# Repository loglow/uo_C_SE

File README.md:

# µo_C SE (uo_C, Ornament & Crime) Eurorack [Rev B]

## 8HP Eurorack module | Polymorphic CV generator

[μo_C SE](http://uoc-se.com) is a multi-purpose module in which a generic set of inputs and outputs are remapped on-the-fly through the use of a number of different built-in apps.

This re-engineered Eurorack module updates and simplifies the classic [Ornament & Crime](http://ornament-and-cri.me/) (aka o_C) design by miniaturizing the module from 14HP to 8HP and redesigning the front panel layout without eliminating any functionality.

Fully compatible with upstream o_C firmware. Includes power cable, mounting hardware, and a one-year warranty. Designed and built with care by [Tall Dog Electronics](http://tall-dog.com) in Western Massachusetts. Licensed [CC BY-NC-SA 4.0](https://creativecommons.org/licenses/by-nc-sa/4.0/) open source hardware.

- **Height:** 3U (128.5 mm)
- **Width:** 8HP (40.3 mm)
- **Depth:** 31 mm (with power)
- **+12V:** 85 mA (average)
- **-12V:** 10 mA (average)

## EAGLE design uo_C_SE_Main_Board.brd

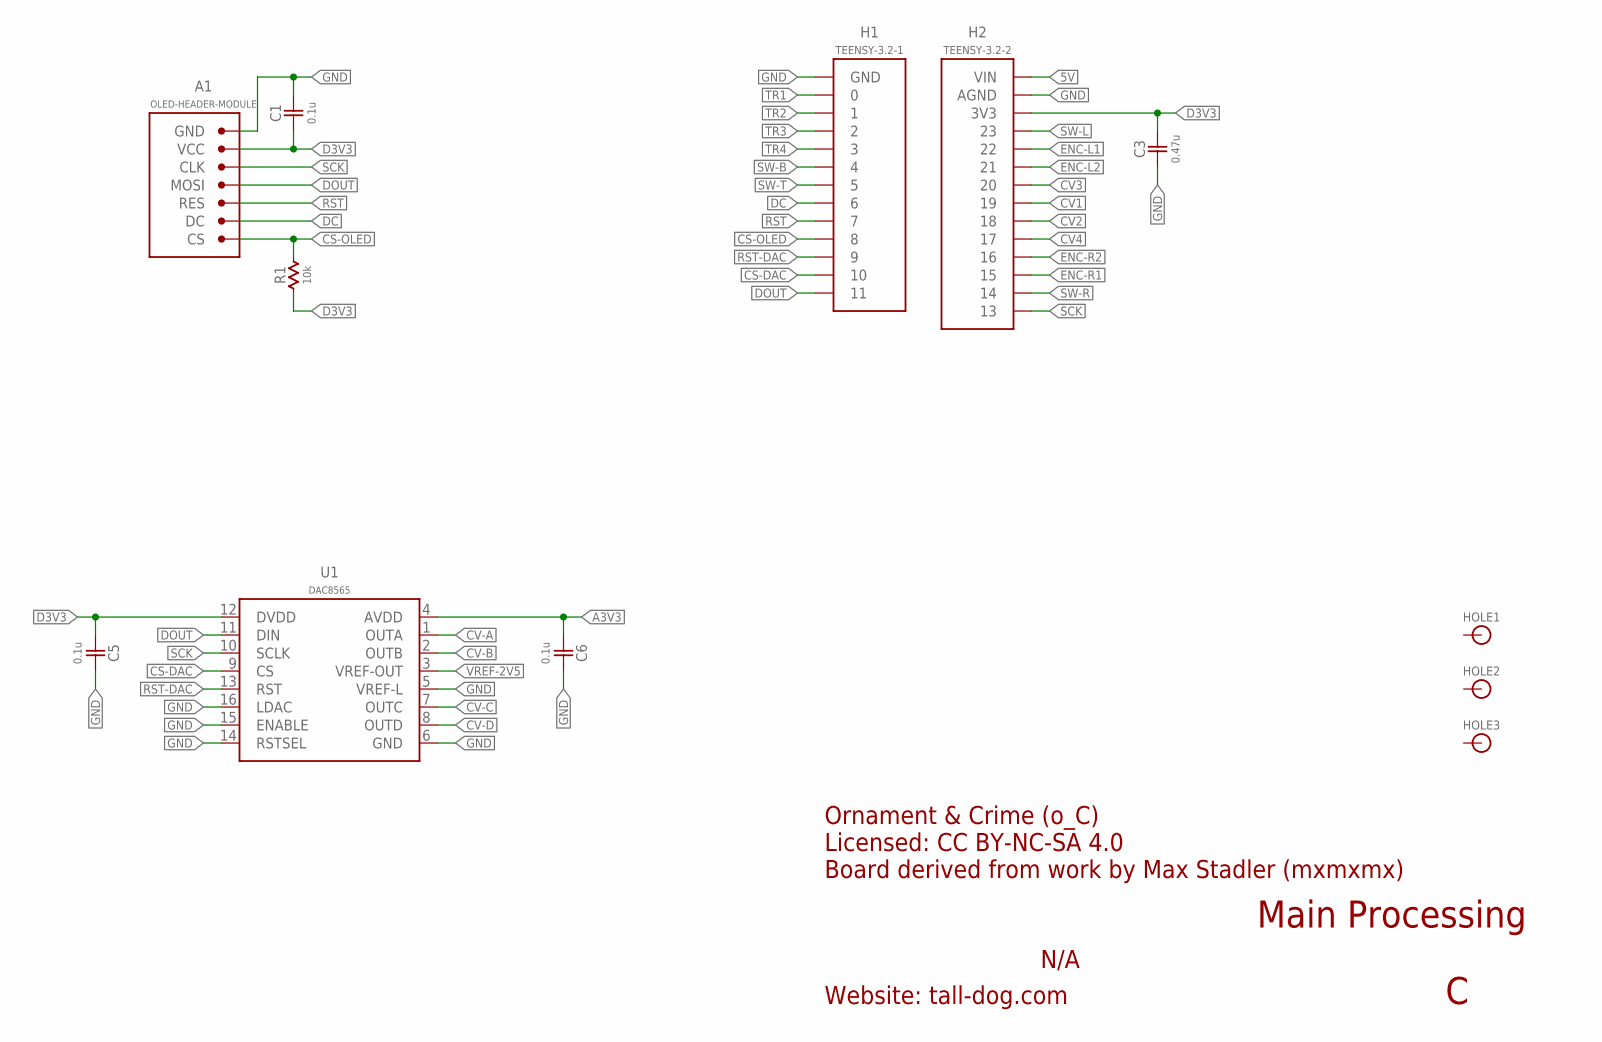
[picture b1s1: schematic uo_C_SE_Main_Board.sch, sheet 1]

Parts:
A1: OLED-HEADER-MODULE; DISPLAY-MODULE; MANUFACTURERPARTNUMBER TD-OCSE-B-DM
C1, C5, C6: 0.1u; 0603-NP; MANUFACTURERPARTNUMBER CL10B104JB8NNNC
C3: 0.47u; 0603-NP; MANUFACTURERPARTNUMBER CL10B474KA8NFNC
H1: TEENSY-3.2-1; SMD-0.1-1X13; MANUFACTURERPARTNUMBER TSM-113-04-L-SV
H2: TEENSY-3.2-2; SMD-0.1-1X14; MANUFACTURERPARTNUMBER TSM-114-04-L-SV
HOLE1, HOLE2, HOLE3: HOLE; M2.5-HOLE
R1: 10k; 0603-NP; MANUFACTURERPARTNUMBER ERJ-3EKF1002V
U1: DAC8565; TSSOP-16; MANUFACTURERPARTNUMBER DAC8565IAPW

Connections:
5V: H2.1 (VIN); also elsewhere on the board
A3V3: C6.1, U1.4 (AVDD); also elsewhere on the board
CS-DAC: H1.12 (10), U1.9 (CS)
CS-OLED: A1.7 (CS), H1.10 (8), R1.2
CV1: H2.8 (19); also elsewhere on the board
CV2: H2.9 (18); also elsewhere on the board
CV3: H2.7 (20); also elsewhere on the board
CV4: H2.10 (17); also elsewhere on the board
CV-A: U1.1 (OUTA); also elsewhere on the board
CV-B: U1.2 (OUTB); also elsewhere on the board
CV-C: U1.7 (OUTC); also elsewhere on the board
CV-D: U1.8 (OUTD); also elsewhere on the board
D3V3: A1.2 (VCC), C1.1, C3.2, C5.1, H2.3 (3V3), R1.1, U1.12 (DVDD)
DC: A1.6 (DC), H1.8 (6)
DOUT: A1.4 (MOSI), H1.13 (11), U1.11 (DIN)
ENC-L1: H2.5 (22); also elsewhere on the board
ENC-L2: H2.6 (21); also elsewhere on the board
ENC-R1: H2.12 (15); also elsewhere on the board
ENC-R2: H2.11 (16); also elsewhere on the board
GND: A1.1 (GND), A1.G1 (GND), A1.G2 (GND), A1.G3 (GND), A1.G4 (GND), A1.G5 (GND), A1.G6 (GND), C1.2, C3.1, C5.2, C6.2, H1.1 (GND), H2.2 (AGND), U1.5 (VREF-L), U1.6 (GND), U1.14 (RSTSEL), U1.15 (ENABLE), U1.16 (LDAC); also elsewhere on the board
RST: A1.5 (RES), H1.9 (7)
RST-DAC: H1.11 (9), U1.13 (RST)
SCK: A1.3 (CLK), H2.14 (13), U1.10 (SCLK)
SW-B: H1.6 (4); also elsewhere on the board
SW-L: H2.4 (23); also elsewhere on the board
SW-R: H2.13 (14); also elsewhere on the board
SW-T: H1.7 (5); also elsewhere on the board
TR1: H1.2 (0); also elsewhere on the board
TR2: H1.3 (1); also elsewhere on the board
TR3: H1.4 (2); also elsewhere on the board
TR4: H1.5 (3); also elsewhere on the board
VREF-2V5: U1.3 (VREF-OUT); also elsewhere on the board

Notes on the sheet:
Ornament & Crime (o_C) Licensed: CC BY-NC-SA 4.0 Board derived from work by Max Stadler (mxmxmx)
Website: tall-dog.com
N/A
Main Processing

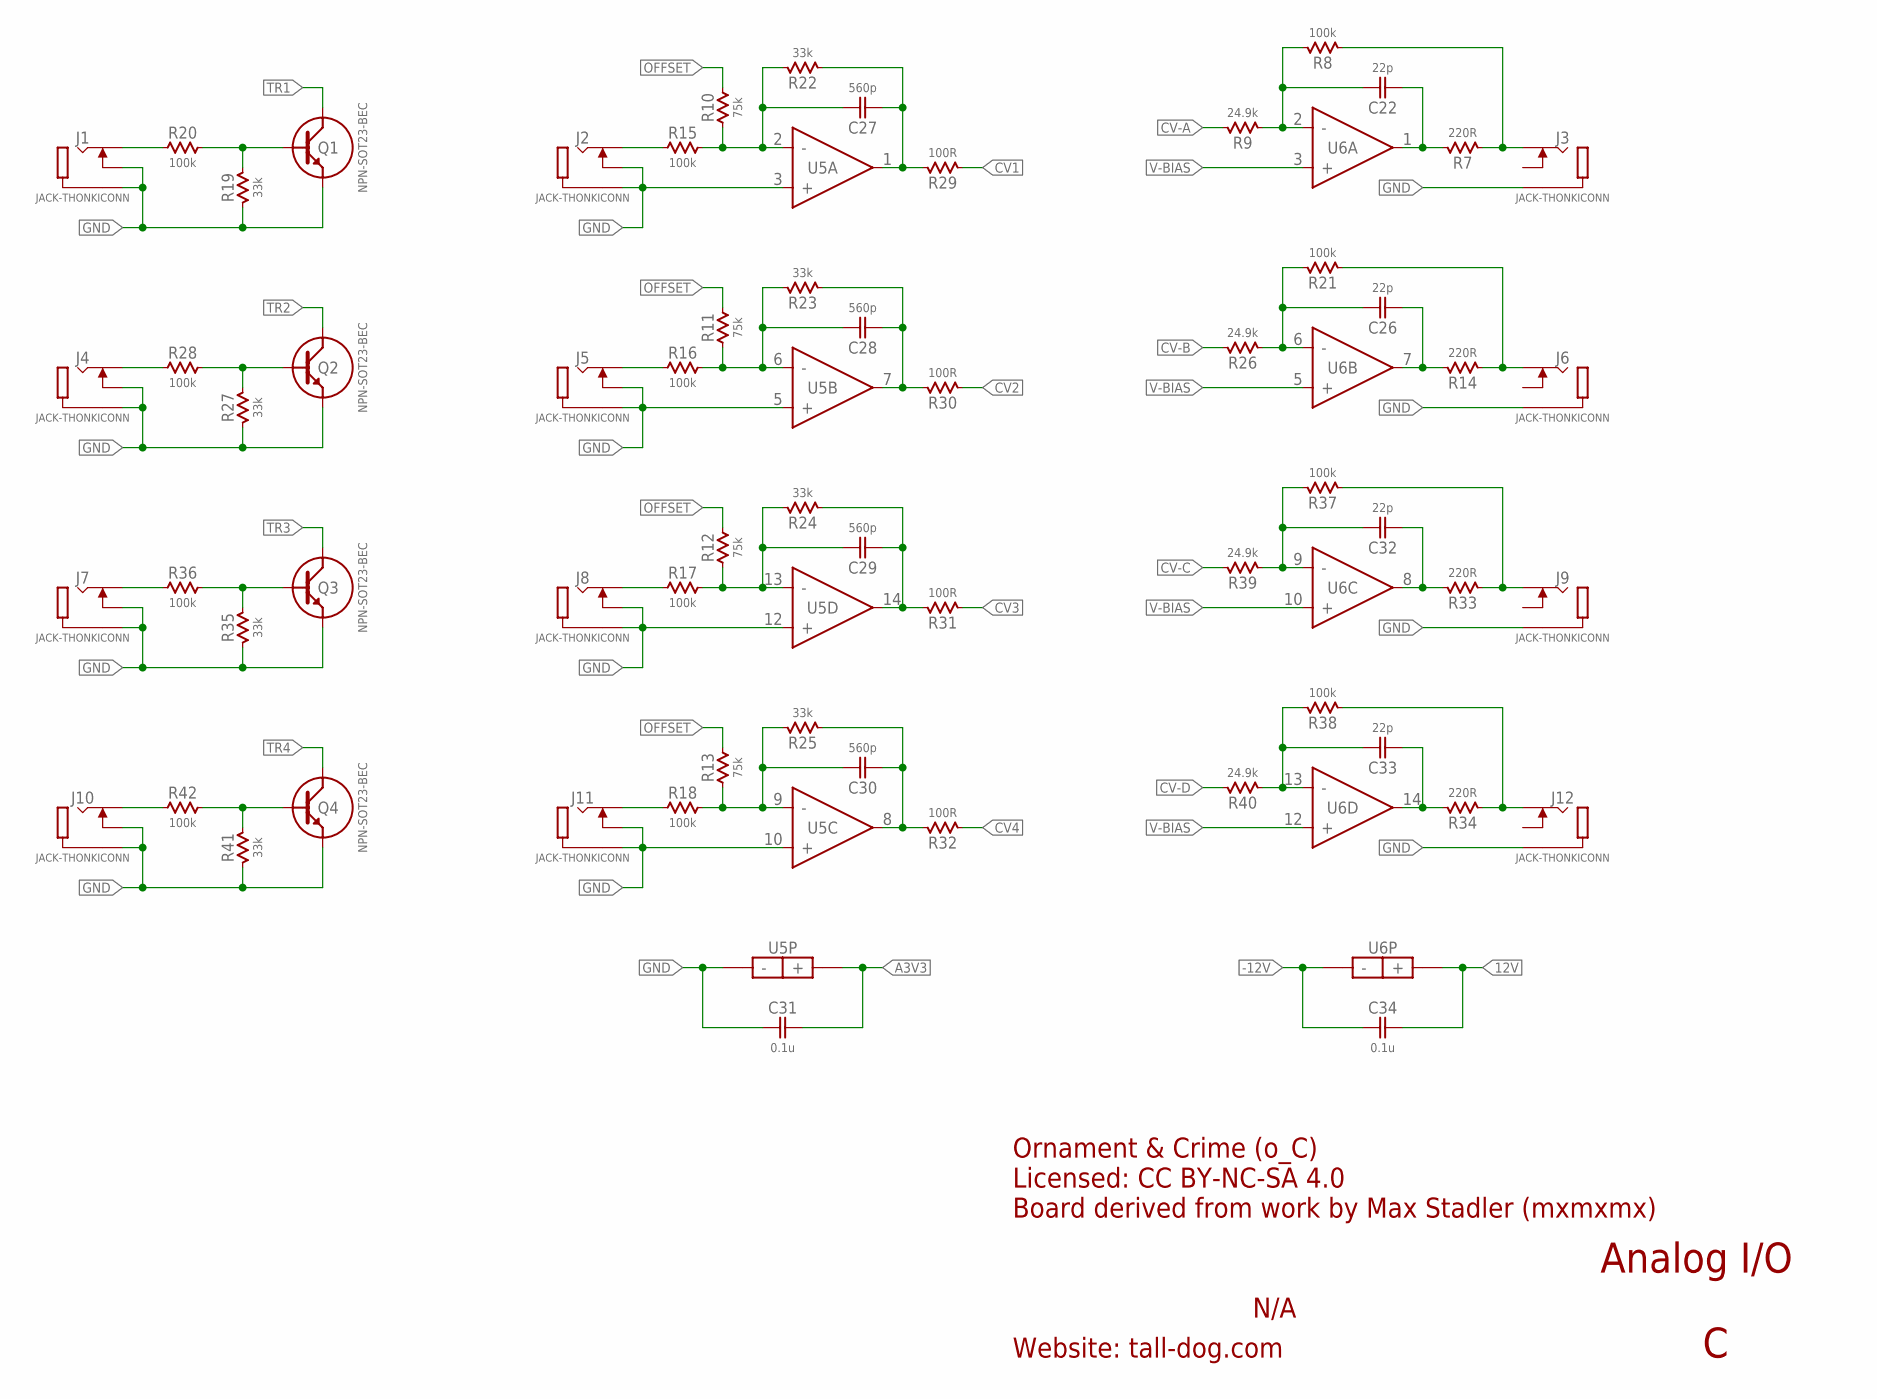
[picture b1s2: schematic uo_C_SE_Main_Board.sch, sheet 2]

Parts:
C22, C26, C32, C33: 22p; 0603-NP; MANUFACTURERPARTNUMBER CL10C220FB8NNWC
C27, C28, C29, C30: 560p; 0603-NP; MANUFACTURERPARTNUMBER CL10C561JB8NNNC
C31, C34: 0.1u; 0603-NP; MANUFACTURERPARTNUMBER CL10B104JB8NNNC
J1: JACK-THONKICONN; JACK; MANUFACTURERPARTNUMBER WQP-PJ398SM
J2, J3, J4, J5, J6, J7, J8, J9, J10, J11, J12: JACK-THONKICONN; JACK
Q1, Q2, Q3, Q4: NPN-SOT23-BEC; SOT-23-3
R7, R14, R33, R34: 220R; 0603-NP; MANUFACTURERPARTNUMBER ERJ-3EKF2200V
R8, R15, R16, R17, R18, R20, R21, R28, R36, R37, R38, R42: 100k; 0603-NP; MANUFACTURERPARTNUMBER ERA-3AEB104V
R9, R26, R39, R40: 24.9k; 0603-NP; MANUFACTURERPARTNUMBER ERA-3AEB2492V
R10, R11, R12, R13: 75k; 0603-NP; MANUFACTURERPARTNUMBER ERJ-3EKF7502V
R19, R22, R23, R24, R25, R27, R35, R41: 33k; 0603-NP; MANUFACTURERPARTNUMBER ERJ-3EKF3302V
R29, R30, R31, R32: 100R; 0603-NP; MANUFACTURERPARTNUMBER ERJ-3EKF1000V
U5: MCP6004-TSSOP-14; TSSOP-14
U6: OPA4172; TSSOP-14

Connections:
12V: C34.1, U6.4 (+); also elsewhere on the board
-12V: C34.2, U6.11 (-); also elsewhere on the board
A3V3: C31.1, U5.4 (+); also elsewhere on the board
CV1: R29.2; also elsewhere on the board
CV2: R30.2; also elsewhere on the board
CV3: R31.2; also elsewhere on the board
CV4: R32.2; also elsewhere on the board
CV-A: R9.1; also elsewhere on the board
CV-B: R26.1; also elsewhere on the board
CV-C: R39.1; also elsewhere on the board
CV-D: R40.1; also elsewhere on the board
GND: C31.2, J1.P1 (1), J1.P2 (2), J2.P1 (1), J2.P2 (2), J3.P1 (1), J4.P1 (1), J4.P2 (2), J5.P1 (1), J5.P2 (2), J6.P1 (1), J7.P1 (1), J7.P2 (2), J8.P1 (1), J8.P2 (2), J9.P1 (1), J10.P1 (1), J10.P2 (2), J11.P1 (1), J11.P2 (2), J12.P1 (1), Q1.2 (E), Q2.2 (E), Q3.2 (E), Q4.2 (E), R19.2, R27.2, R35.2, R41.2, U5.3 (+), U5.5 (+), U5.10 (+), U5.11 (-), U5.12 (+); also elsewhere on the board
unnamed: J11.P3 (3), R18.1
unnamed: J8.P3 (3), R17.1
unnamed: J5.P3 (3), R16.1
unnamed: J2.P3 (3), R15.1
unnamed: J1.P3 (3), R20.1
unnamed: C27.1, R10.1, R15.2, R22.1, U5.2 (-)
unnamed: Q1.1 (B), R19.1, R20.2
unnamed: C28.1, R11.1, R16.2, R23.1, U5.6 (-)
unnamed: C29.1, R12.1, R17.2, R24.1, U5.13 (-)
unnamed: C22.2, R8.1, R9.2, U6.2 (-)
unnamed: C30.1, R13.1, R18.2, R25.1, U5.9 (-)
unnamed: J4.P3 (3), R28.1
unnamed: C27.2, R22.2, R29.1, U5.1 (OUT)
unnamed: C28.2, R23.2, R30.1, U5.7 (OUT)
unnamed: Q2.1 (B), R27.1, R28.2
unnamed: C29.2, R24.2, R31.1, U5.14 (OUT)
unnamed: C30.2, R25.2, R32.1, U5.8 (OUT)
unnamed: C26.2, R21.1, R26.2, U6.6 (-)
unnamed: J7.P3 (3), R36.1
unnamed: Q3.1 (B), R35.1, R36.2
unnamed: C32.2, R37.1, R39.2, U6.9 (-)
unnamed: C33.2, R38.1, R40.2, U6.13 (-)
unnamed: J10.P3 (3), R42.1
unnamed: Q4.1 (B), R41.1, R42.2
unnamed: C22.1, R7.1, U6.1 (OUT)
unnamed: C26.1, R14.1, U6.7 (OUT)
unnamed: C32.1, R33.1, U6.8 (OUT)
unnamed: C33.1, R34.1, U6.14 (OUT)
unnamed: J3.P3 (3), R7.2, R8.2
unnamed: J6.P3 (3), R14.2, R21.2
unnamed: J9.P3 (3), R33.2, R37.2
unnamed: J12.P3 (3), R34.2, R38.2
OFFSET: R10.2, R11.2, R12.2, R13.2; also elsewhere on the board
TR1: Q1.3 (C); also elsewhere on the board
TR2: Q2.3 (C); also elsewhere on the board
TR3: Q3.3 (C); also elsewhere on the board
TR4: Q4.3 (C); also elsewhere on the board
V-BIAS: U6.3 (+), U6.5 (+), U6.10 (+), U6.12 (+); also elsewhere on the board

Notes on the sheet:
Ornament & Crime (o_C) Licensed: CC BY-NC-SA 4.0 Board derived from work by Max Stadler (mxmxmx)
Website: tall-dog.com
N/A
Analog I/O

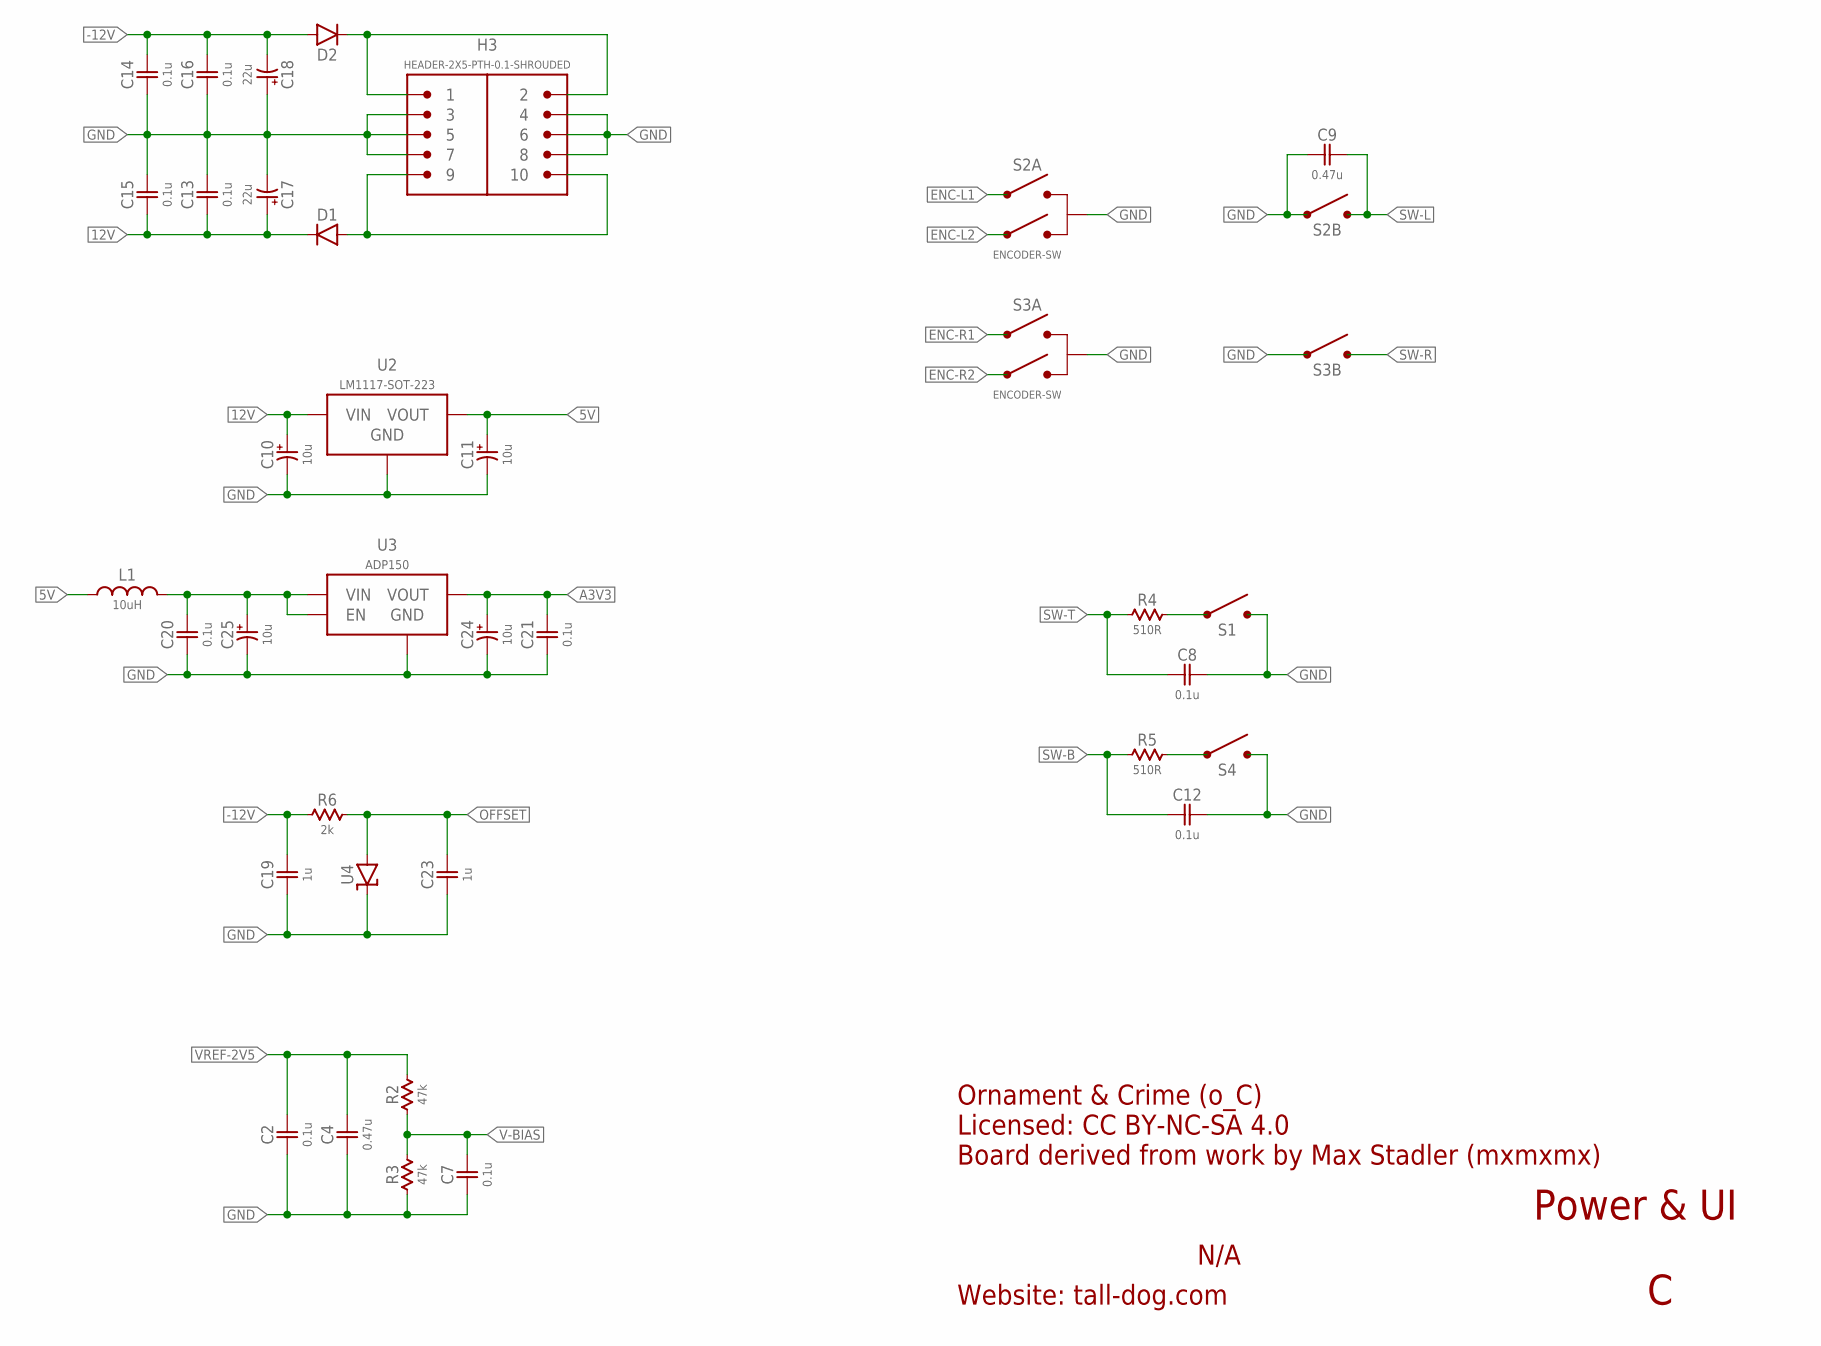
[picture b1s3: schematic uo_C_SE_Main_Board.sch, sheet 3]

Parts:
C2, C7, C8, C12, C13, C14, C15, C16, C20, C21: 0.1u; 0603-NP; MANUFACTURERPARTNUMBER CL10B104JB8NNNC
C4, C9: 0.47u; 0603-NP; MANUFACTURERPARTNUMBER CL10B474KA8NFNC
C10, C11, C24, C25: 10u; ELECTRO-SMD-4.3MM; MANUFACTURERPARTNUMBER 865230440002
C17, C18: 22u; ELECTRO-SMD-6.6MM; MANUFACTURERPARTNUMBER 865230443003
C19, C23: 1u; 0603-NP; MANUFACTURERPARTNUMBER CL10B105KA8NNNC
D1, D2: DIODE-SOD123; SOD-123
H3: HEADER-2X5-PTH-0.1-SHROUDED; PTH-0.1-2X5-SHROUDED
L1: 10uH; 1210-NP; MANUFACTURERPARTNUMBER NLCV32T-100K-PFR
R2, R3: 47k; 0603-NP; MANUFACTURERPARTNUMBER ERJ-3EKF4702V
R4, R5: 510R; 0603-NP; MANUFACTURERPARTNUMBER ERJ-3EKF5100V
R6: 2k; 0603-NP; MANUFACTURERPARTNUMBER ERJ-3EKF2001V
S1, S4: SPST-PTH; TL1105
S2, S3: ENCODER-SW; ENCODER-EC12E
U2: LM1117-SOT-223; SOT-223
U3: ADP150; SOT-23-5
U4: LM4040-SOT-23; SOT-23-3

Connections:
5V: C11.A (POS), L1.1, U2.2 (VOUT), U2.4 (VOUT); also elsewhere on the board
12V: C10.A (POS), C13.1, C15.1, C17.A (POS), D1.C, U2.3 (VIN); also elsewhere on the board
-12V: C14.2, C16.2, C18.C (NEG), C19.1, D2.A, R6.1; also elsewhere on the board
A3V3: C21.2, C24.A (POS), U3.5 (VOUT); also elsewhere on the board
ENC-L1: S2.B; also elsewhere on the board
ENC-L2: S2.A; also elsewhere on the board
ENC-R1: S3.B; also elsewhere on the board
ENC-R2: S3.A; also elsewhere on the board
GND: C2.2, C4.2, C7.2, C8.2, C9.1, C10.C (NEG), C11.C (NEG), C12.2, C13.2, C14.1, C15.2, C16.1, C17.C (NEG), C18.A (POS), C19.2, C20.1, C21.1, C23.2, C24.C (NEG), C25.C (NEG), H3.3, H3.4, H3.5, H3.6, H3.7, H3.8, R3.1, S1.3 (2), S1.4 (2), S2.C, S2.D (1), S3.C, S3.D (1), S4.3 (2), S4.4 (2), U2.1 (GND), U3.2 (GND), U4.1 (C); also elsewhere on the board
unnamed: C20.2, C25.A (POS), L1.2, U3.1 (VIN), U3.3 (EN)
unnamed: D2.C, H3.1, H3.2
unnamed: D1.A, H3.9, H3.10
unnamed: R4.2, S1.1, S1.2 (1)
unnamed: R5.2, S4.1, S4.2 (1)
OFFSET: C23.1, R6.2, U4.2 (A); also elsewhere on the board
SW-B: C12.1, R5.1; also elsewhere on the board
SW-L: C9.2, S2.E (2); also elsewhere on the board
SW-R: S3.E (2); also elsewhere on the board
SW-T: C8.1, R4.1; also elsewhere on the board
V-BIAS: C7.1, R2.1, R3.2; also elsewhere on the board
VREF-2V5: C2.1, C4.1, R2.2; also elsewhere on the board

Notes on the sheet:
Ornament & Crime (o_C) Licensed: CC BY-NC-SA 4.0 Board derived from work by Max Stadler (mxmxmx)
Website: tall-dog.com
N/A
Power & UI

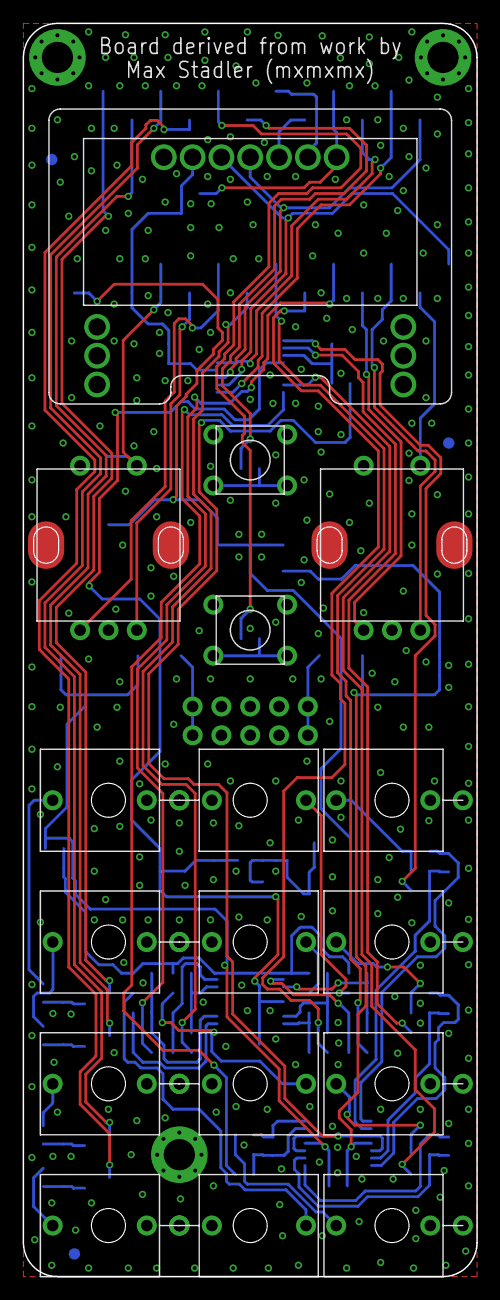
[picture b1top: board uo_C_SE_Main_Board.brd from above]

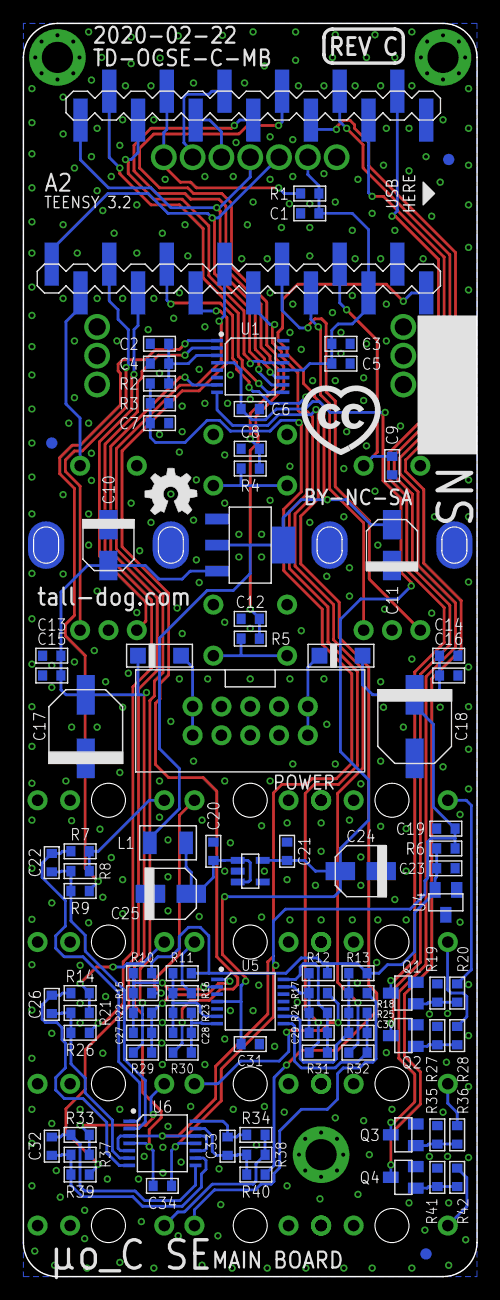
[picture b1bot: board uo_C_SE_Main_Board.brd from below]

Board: 2 copper layers, 40.0 x 110.5 mm, 118 parts (98 on the bottom side), 73 nets.

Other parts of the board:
U$1: LOGO-CC
U$2: LOGO-OSH
U$3: LOGO-REV
U$4, U$5, U$6: FIDUCIAL

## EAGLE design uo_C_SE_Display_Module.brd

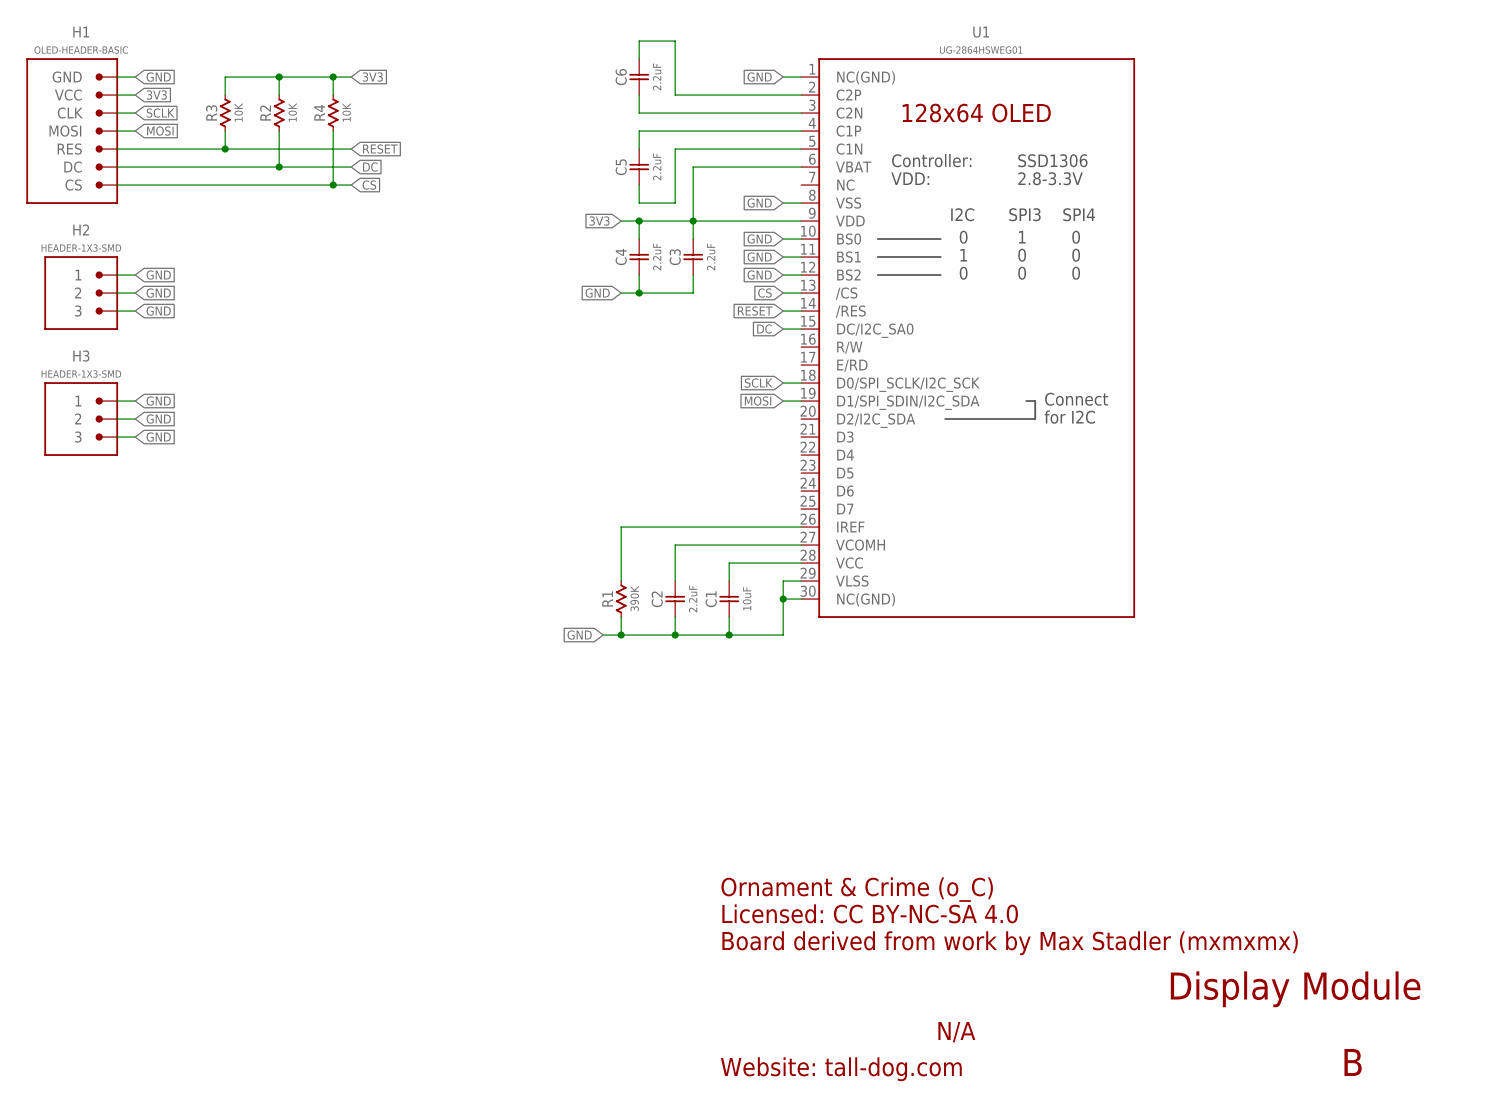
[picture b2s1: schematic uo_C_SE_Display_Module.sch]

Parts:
C1: 10uF; 0805-NP
C2, C3, C4, C5, C6: 2.2uF; 0805-NP
H1: OLED-HEADER-BASIC; SMD-0.1-1X7
H2, H3: HEADER-1X3-SMD; SMD-0.1-1X3
R1: 390K; 0805-NP
R2, R3, R4: 10K; 0805-NP
U1: UG-2864HSWEG01; OLED-128X64

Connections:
3V3: C3.2, C4.2, H1.2 (VCC), R2.2, R3.2, R4.2, U1.6 (VBAT), U1.9 (VDD)
CS: H1.7 (CS), R4.1, U1.13 (/CS)
DC: H1.6 (DC), R2.1, U1.15 (DC/I2C_SA0)
GND: C1.1, C2.1, C3.1, C4.1, H1.1 (GND), H2.1, H2.2, H2.3, H3.1, H3.2, H3.3, R1.1, U1.1 (NC(GND)), U1.8 (VSS), U1.10 (BS0), U1.11 (BS1), U1.12 (BS2), U1.29 (VLSS), U1.30 (NC(GND))
MOSI: H1.4 (MOSI), U1.19 (D1/SPI_SDIN/I2C_SDA)
unnamed: R1.2, U1.26 (IREF)
unnamed: C6.2, U1.2 (C2P)
unnamed: C6.1, U1.3 (C2N)
unnamed: C5.2, U1.4 (C1P)
unnamed: C5.1, U1.5 (C1N)
unnamed: C1.2, U1.28 (VCC)
unnamed: C2.2, U1.27 (VCOMH)
RESET: H1.5 (RES), R3.1, U1.14 (/RES)
SCLK: H1.3 (CLK), U1.18 (D0/SPI_SCLK/I2C_SCK)

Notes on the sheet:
Ornament & Crime (o_C) Licensed: CC BY-NC-SA 4.0 Board derived from work by Max Stadler (mxmxmx)
Website: tall-dog.com
N/A
Display Module

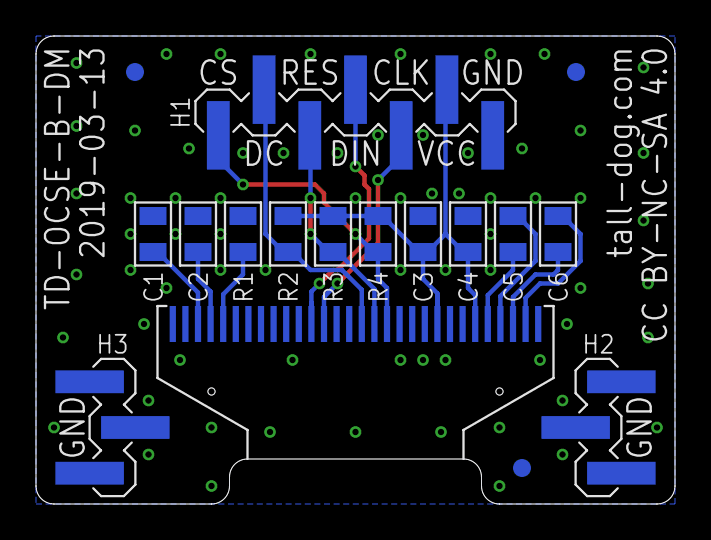
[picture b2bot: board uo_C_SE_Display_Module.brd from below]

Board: 2 copper layers, 35.5 x 26.0 mm, 17 parts (16 on the bottom side), 14 nets.

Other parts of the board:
U$1, U$2, U$3: FIDUCIAL

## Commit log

2018-11-17 initial commit, revision B production
2019-07-12 assembly process updates
2021-03-23 Revision C
